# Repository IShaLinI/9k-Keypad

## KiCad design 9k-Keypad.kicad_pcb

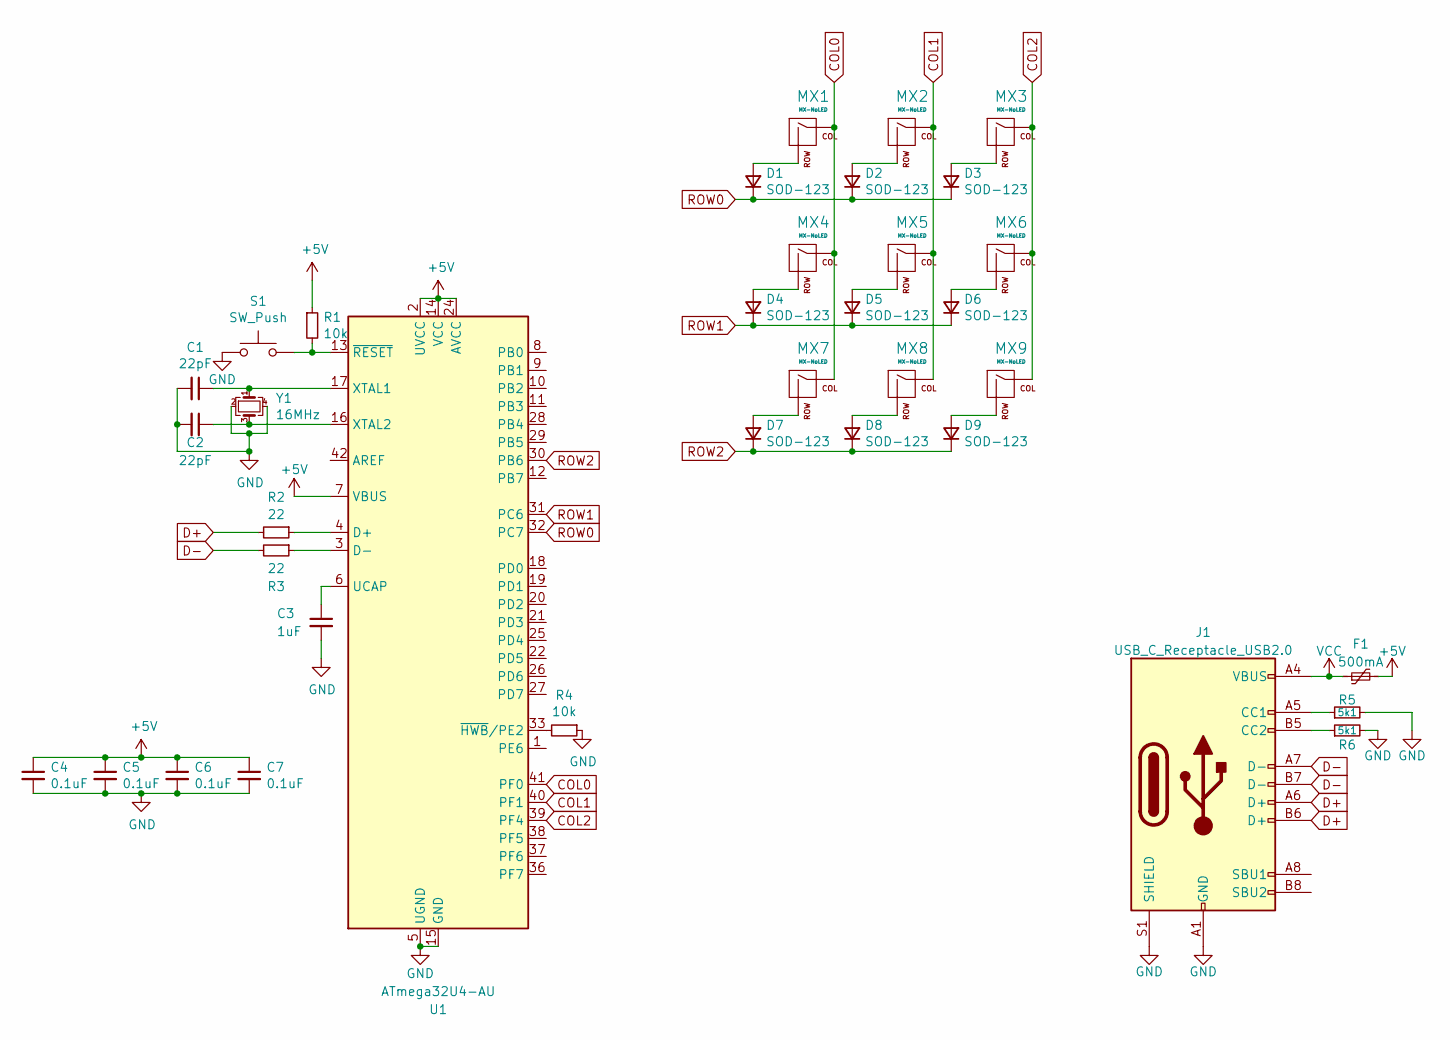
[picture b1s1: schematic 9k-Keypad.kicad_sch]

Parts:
C1, C2: 22pF; C_0805_2012Metric
C3: 1uF; C_0805_2012Metric
C4, C5, C6, C7: 0.1uF; C_0805_2012Metric
D1, D2, D3, D4, D5, D6, D7, D8, D9: SOD-123; D_SOD-123
F1: 500mA; Fuse_0805_2012Metric
J1: USB_C_Receptacle_USB2.0; USB_C_Receptacle_HRO_TYPE-C-31-M-12
MX1, MX2, MX3, MX4, MX5, MX6, MX7, MX8, MX9: MX-NoLED; MXOnly-1U-NoLED
R1, R4: 10k; R_0805_2012Metric
R2, R3: 22; R_0805_2012Metric
R5, R6: 5k1; R_0805_2012Metric
S1: SW_Push; SKQG-1155865
U1: ATmega32U4-AU; TQFP-44_10x10mm_P0.8mm
Y1: 16MHz; Crystal_SMD_3225-4Pin_3.2x2.5mm

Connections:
+5V: C4.1, C5.1, C6.1, C7.1, F1.2, R1.1, U1.2 (UVCC), U1.7 (VBUS), U1.14 (VCC), U1.24 (AVCC), U1.34 (VCC), U1.44 (AVCC)
COL0: MX1.1 (COL), MX4.1 (COL), MX7.1 (COL), U1.41 (PF0)
COL1: MX2.1 (COL), MX5.1 (COL), MX8.1 (COL), U1.40 (PF1)
COL2: MX3.1 (COL), MX6.1 (COL), MX9.1 (COL), U1.39 (PF4)
D+: J1.A6 (D+), J1.B6 (D+), R2.2
D-: J1.A7 (D-), J1.B7 (D-), R3.2
GND: C1.2, C2.2, C3.2, C4.2, C5.2, C6.2, C7.2, J1.A1 (GND), J1.A12 (GND), J1.B1 (GND), J1.B12 (GND), J1.S1 (SHIELD), R4.1, R5.2, R6.2, S1.1, U1.5 (UGND), U1.15 (GND), U1.23 (GND), U1.35 (GND), U1.43 (GND), Y1.2, Y1.4
unnamed: C1.1, U1.17 (XTAL1), Y1.1
unnamed: C2.1, U1.16 (XTAL2), Y1.3
unnamed: C3.1, U1.6 (UCAP)
unnamed: D1.2 (A), MX1.2 (ROW)
unnamed: D2.2 (A), MX2.2 (ROW)
unnamed: D3.2 (A), MX3.2 (ROW)
unnamed: D4.2 (A), MX4.2 (ROW)
unnamed: D5.2 (A), MX5.2 (ROW)
unnamed: D6.2 (A), MX6.2 (ROW)
unnamed: D7.2 (A), MX7.2 (ROW)
unnamed: D8.2 (A), MX8.2 (ROW)
unnamed: D9.2 (A), MX9.2 (ROW)
unnamed: J1.A5 (CC1), R5.1
unnamed: J1.B5 (CC2), R6.1
unnamed: R1.2, S1.2, U1.13 (~RESET)
unnamed: R2.1, U1.4 (D+)
unnamed: R3.1, U1.3 (D-)
unnamed: R4.2, U1.33 (~HWB/PE2)
ROW0: D1.1 (K), D2.1 (K), D3.1 (K), U1.32 (PC7)
ROW1: D4.1 (K), D5.1 (K), D6.1 (K), U1.31 (PC6)
ROW2: D7.1 (K), D8.1 (K), D9.1 (K), U1.30 (PB6)
VCC: F1.1, J1.A4 (VBUS), J1.A9 (VBUS), J1.B4 (VBUS), J1.B9 (VBUS)

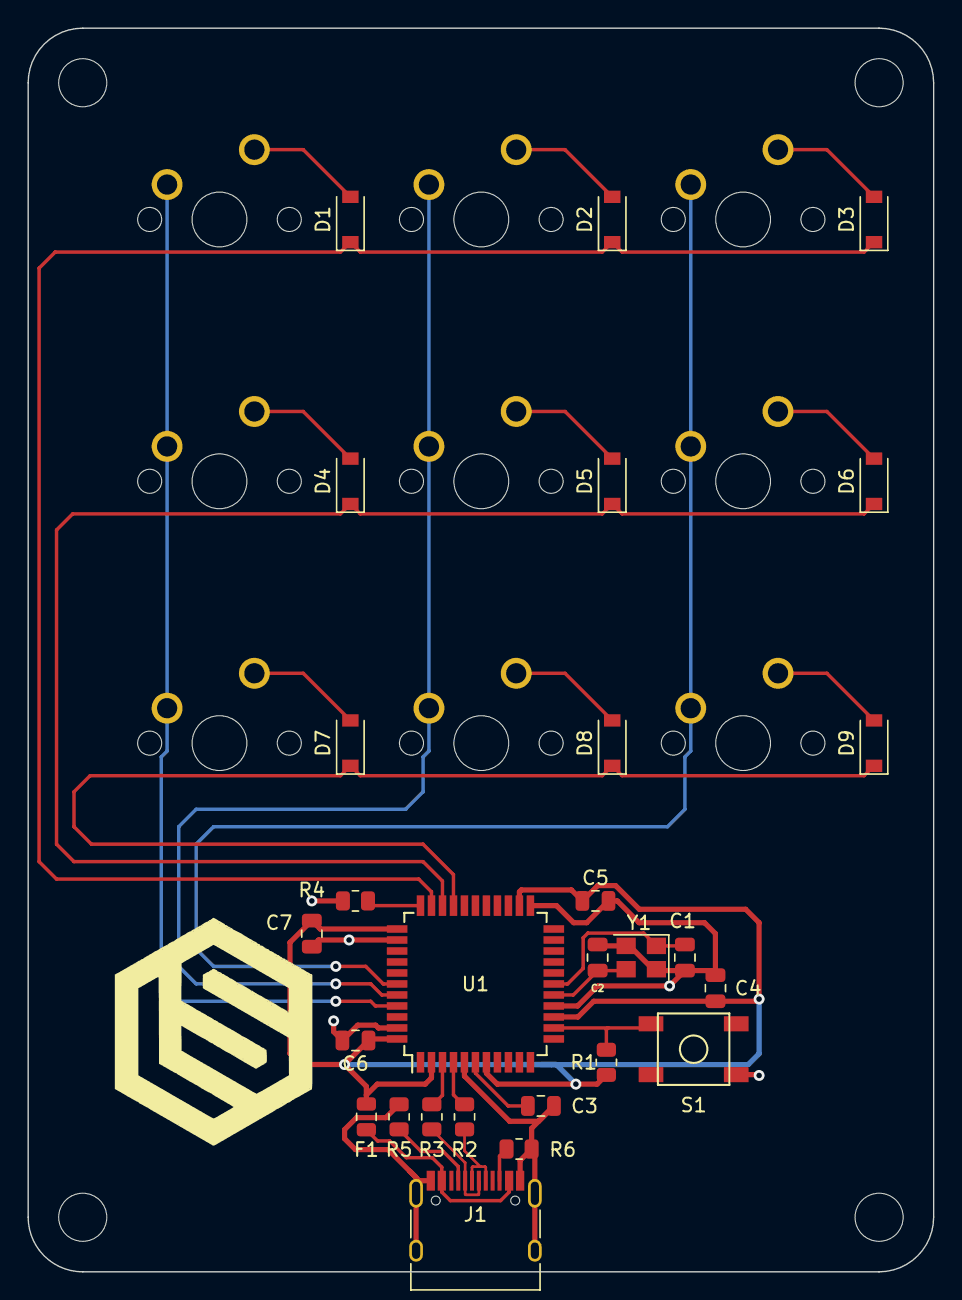
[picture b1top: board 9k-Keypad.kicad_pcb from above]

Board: 2 copper layers, 65.9 x 90.5 mm, 36 parts (0 on the bottom side), 29 nets.

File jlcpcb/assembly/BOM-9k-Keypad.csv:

Comment,Designator,Footprint,LCSC
MX-NoLED,MX5,MXOnly-1U-NoLED,
10k,R4,R_0805_2012Metric,
MX-NoLED,MX8,MXOnly-1U-NoLED,
22,R3,R_0805_2012Metric,
SOD-123,D2,D_SOD-123,
MX-NoLED,MX7,MXOnly-1U-NoLED,
22pF,C1,C_0805_2012Metric,
SOD-123,D7,D_SOD-123,
SOD-123,D8,D_SOD-123,
5k1,R5,R_0805_2012Metric,
5k1,R6,R_0805_2012Metric,
MX-NoLED,MX9,MXOnly-1U-NoLED,
MX-NoLED,MX3,MXOnly-1U-NoLED,
USB_C_Receptacle_USB2.0,J1,USB_C_Receptacle_HRO_TYPE-C-31-M-12,
22pF,C2,C_0805_2012Metric,
MX-NoLED,MX6,MXOnly-1U-NoLED,
0.1uF,C7,C_0805_2012Metric,
10k,R1,R_0805_2012Metric,
1uF,C3,C_0805_2012Metric,
SOD-123,D5,D_SOD-123,
0.1uF,C4,C_0805_2012Metric,
500mA,F1,Fuse_0805_2012Metric,
SOD-123,D3,D_SOD-123,
22,R2,R_0805_2012Metric,
SW_Push,S1,SKQG-1155865,
SOD-123,D9,D_SOD-123,
SOD-123,D6,D_SOD-123,
SOD-123,D4,D_SOD-123,
MX-NoLED,MX2,MXOnly-1U-NoLED,
MX-NoLED,MX4,MXOnly-1U-NoLED,
0.1uF,C5,C_0805_2012Metric,
ATmega32U4-AU,U1,TQFP-44_10x10mm_P0.8mm,
16MHz,Y1,Crystal_SMD_3225-4Pin_3.2x2.5mm,
0.1uF,C6,C_0805_2012Metric,
SOD-123,D1,D_SOD-123,
MX-NoLED,MX1,MXOnly-1U-NoLED,

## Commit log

2022-10-07 KiCad project creation
2022-10-07 Add submodules
2022-10-07 changed directorys
2022-10-07 added part libraries to KiCad project
2022-10-07 new layout and USB-C
2022-10-07 compacted layouyt
2022-10-08 updated kiCad to 6.0.8 and compacted layout
2022-10-08 removed old project
2022-10-08 revert to only kiCad 6 project
2022-10-08 fix various routing issues
2022-10-08 Finished Design
